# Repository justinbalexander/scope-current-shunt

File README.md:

# Current monitor

## Description

This project implements a simple current sensor to measure the current draw of
some low power sensor nodes. The devices can be hooked up to an oscilloscope
and the current draw recorded to get another window into the device operation
over time.

The batteries required are 3V CR123A batteries.

The DUT current draw range should be less than or equal to about 30mV.  The
intention is to watch the current draw using a Siglent SDS1202X-E with the
vertical axis set to 100 mV/div. The expected max Vo is 687.69mV which is
almost all of the screen size of 772mV to minimize quantization error in the
oscilloscope.

## Implementation

The design was described using Skidl and pcb designed using Kicad:

https://github.com/xesscorp/skidl

## Build Instructions

Skidl is required:

```bash
pip3 install skidl
```

To rebuild the netlist for importing into pcbnew:

```bash
./scope-current-shunt.py
```

Open the file scope-current-shunt.kicad_pcb in pcbnew to edit the pcb.

## Render

## Attributions

Some symbols and footprints  came from www.snapeda.com. See the library folder for the required
license and attributions.

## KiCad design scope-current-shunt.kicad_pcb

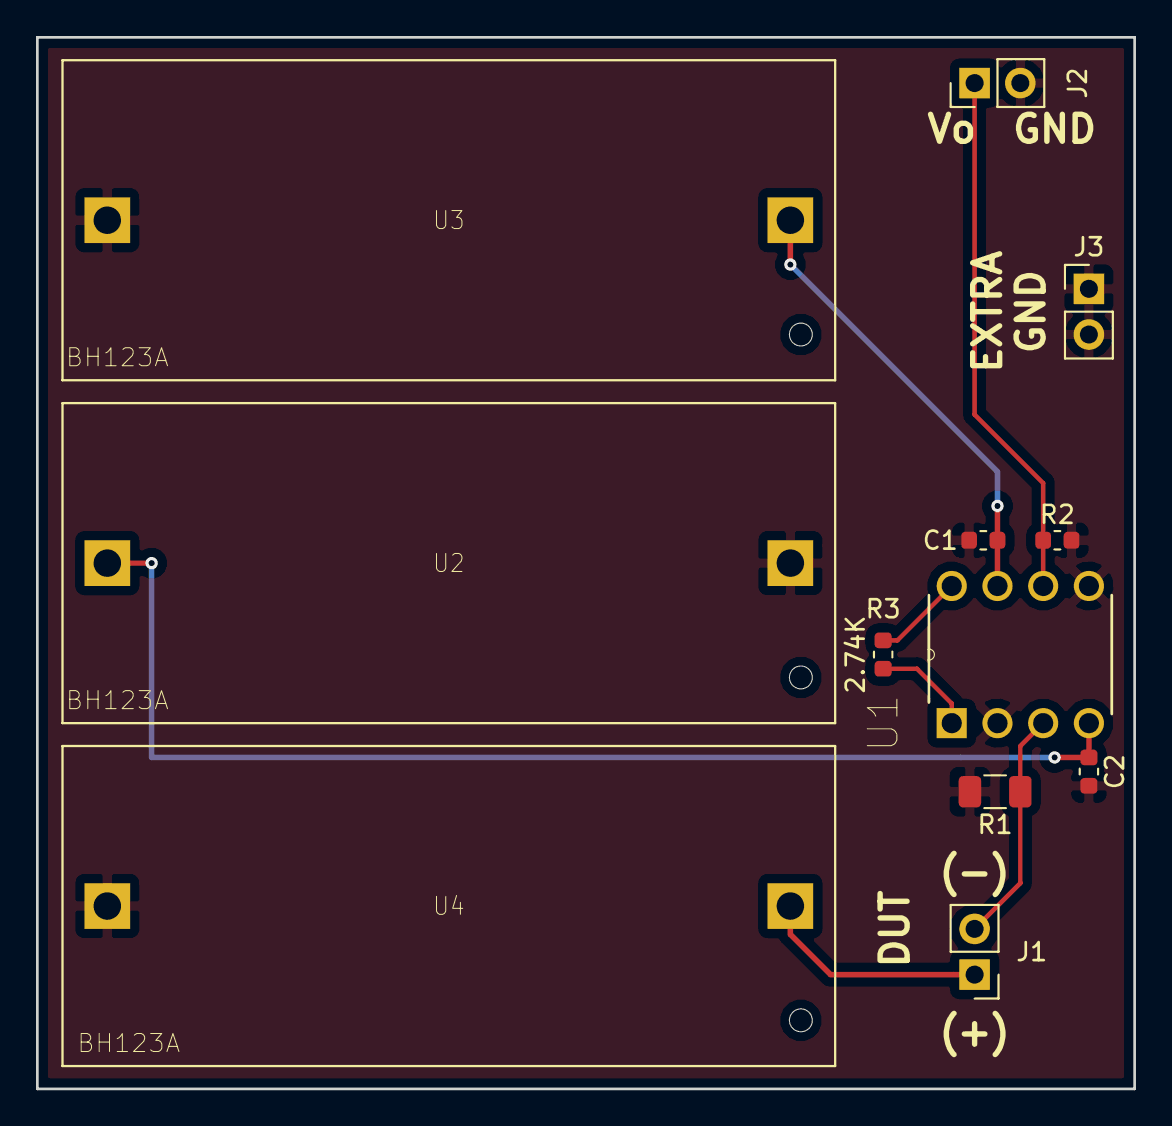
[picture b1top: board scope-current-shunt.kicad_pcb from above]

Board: 2 copper layers, 61.0 x 58.4 mm, 12 parts (0 on the bottom side), 8 nets.

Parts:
C1, C2: 0.1uF; C_0603_1608Metric
J1: Screw_Terminal_01x02; PinHeader_1x02_P2.54mm_Vertical
J2, J3: Conn_01x02_Male; PinHeader_1x02_P2.54mm_Vertical
R1: 1; R_1206_3216Metric
R2: R2.5K; R_0603_1608Metric
R3: 2.74K; R_0603_1608Metric
U1: INA129P; DIP254P762X508-8
U2, U3, U4: BH123A

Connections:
GND: C1.2, C2.2, J2.2, J3.1, J3.2, R1.2, R2.2, U1.2, U1.5, U2.+, U3.-, U4.-
unnamed: R3.1, U1.8
unnamed: R3.2, U1.1
unnamed: J1.2, R1.1, U1.3
V+: C1.1, U1.7, U3.+
V-: C2.1, U1.4, U2.-
VDD: J1.1, U4.+
Vo: J2.1, R2.1, U1.6

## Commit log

2019-05-30 Add empty gitignore and README
2019-06-02 Add INA129 symbol and footprint
2019-06-02 Add empty kicad project files
2019-06-02 Add BH123A CR123 battery holder symbol and footprint
2019-06-02 Add skidl description of circuit
2019-06-03 Generate Gerbers
2019-06-03 First board layout
2019-06-03 ignore output files and swap files
2019-06-03 Fill out README
2019-06-03 Add UNLICENSE
